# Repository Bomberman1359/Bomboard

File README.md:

# Bomboard
This is my cost efficient, custom keyboard made by me. As my first project, I named it Bomboard.

I made this project not only for the Highway programs, but also to gain experience in creating my own electronics.
I wanted to learn more about schematics, wiring, PCB, and 3D modeling. As someone that does not spend money on buying keyboards I figured it would be cool to create my own!

## Schematic

## PCB

## Case

## Case and PCB combined 

## BOM
|    Item    | Quantity | Vendor | Total Price |
| :-------- | :-------: | :----- | ----------: |
| PCB | 1 | JLCPB | $74.23 |
| Raspberry Pi Pico | 1 | [Seeed Studio](https://www.seeedstudio.com/Raspberry-Pi-Pico-2-p-5940.html?srsltid=AfmBOopNDN0RoseM_BDfpGL9q782IZnb89sHLu-LgA_pmGtyh8bIAI12ZJQ&gQT=2) | $5.00 |
| Key switches |  64  |  [Mechanical](https://mechanicalkeyboards.com/products/cherry-mx2a-blue-60g-clicky?_pos=1&_fid=016d7ed23&_ss=c)| $25.60 |
| Rotary Encoder | 1    | [SynthCube](https://synthcube.com/rotary-encoder/?gQT=1) | $2.95 | 
| Stabilizer set | 1 | [Divinikey](https://jlcpcb.com/) | $11.00 |
| Keycaps Set| 1 | [Amazon](https://www.amazon.com/Womier-Pudding-Keycaps-100-Percent/dp/B0DB4Z6DMS/ref=sr_1_4?crid=3KDSGFET7R3PW&dib=eyJ2IjoiMSJ9.JXTwjGdToK3WZEH4x7wFjjcMgp3TTPoNjdzpdxdQVgSHMkKCM3K1UQXigcpua9MdYIqJtKjmeekwVAu9vGDxT6nALVuQltDVwMgUqYsUHxBDTm3vLYU9XO3WX6_CRoCUf1UHvEwgMiXLOVtKKSAhyrsmoaTP-IWt4scI0ptknhSZiXKoMoXzRBTZNzhqpnvYZ7vWStdUbOes3QbC9iO88euB4x_6QWYsmUlvxiN9ol6HuYmnZpW-kDZQ4B3cP-TrFnPHNfEt-rMB7Xzw2pRuJncPvS_wAUjKVpEICK8Bqcc.ESKlCixw82J9ZDOgV03xSDnqUloHnb8AKA523uXzZJI&dib_tag=se&keywords=normal%2Bkey%2Bcaps&qid=1751660071&s=electronics&sprefix=normal%2Bkey%2Bcaps%2Celectronics%2C144&sr=1-4&th=1) | $14.99 |

Net Total Cost: $133.77

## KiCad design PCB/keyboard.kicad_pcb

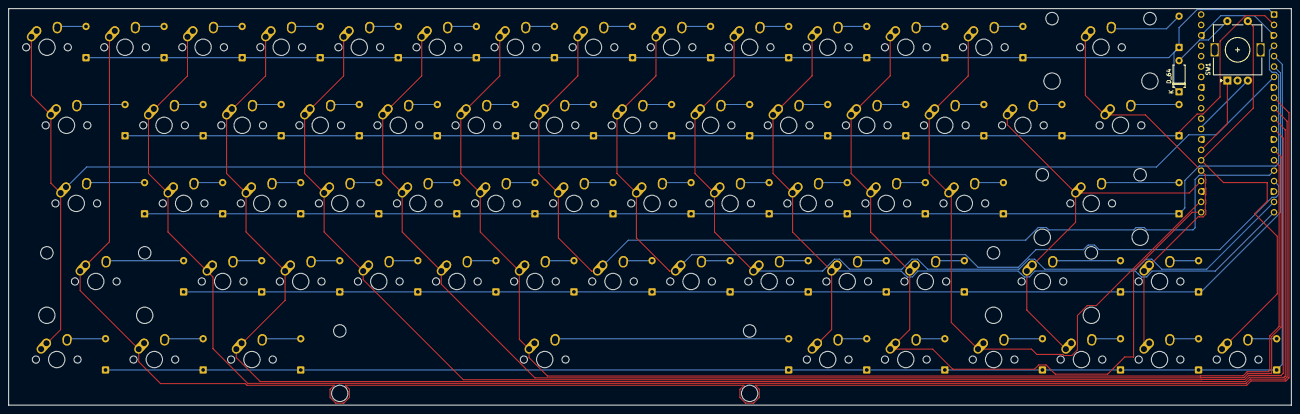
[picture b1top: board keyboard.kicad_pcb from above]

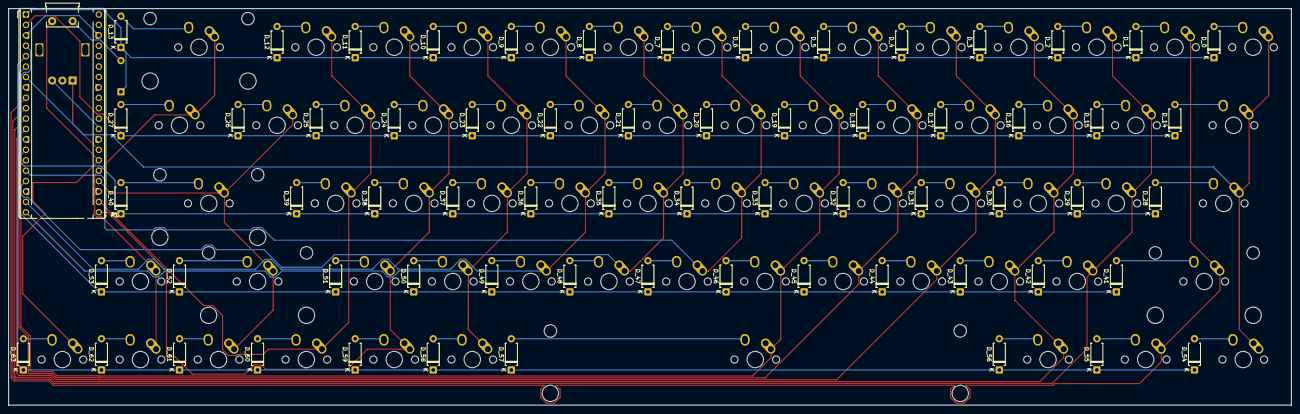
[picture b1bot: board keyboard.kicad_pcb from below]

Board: 2 copper layers, 313.0 x 96.8 mm, 131 parts (65 on the bottom side), 89 nets.

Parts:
A1: RaspberryPi_Pico; RaspberryPi_Pico_Common_THT
D_0, D_1, D_2, D_3, D_4, D_5, D_6, D_7, D_8, D_9, D_10, D_11, D_12, D_13, D_14, D_15, D_16, D_17, D_18, D_19, D_20, D_21, D_22, D_23, D_24, D_25, D_26, D_27, D_28, D_29, D_30, D_31, D_32, D_33, D_34, D_35, D_36, D_37, D_38, D_39, D_40, D_41, D_42, D_43, D_44, D_45, D_46, D_47, D_48, D_49, D_50, D_51, D_52, D_53, D_54, D_55, D_56, D_57, D_58, D_59, D_60, D_61, D_62, D_63, D_64: D; D_A-405_P7.62mm_Horizontal
K_0, K_1, K_2, K_3, K_4, K_5, K_6, K_7, K_8, K_9, K_10, K_11, K_12, K_15, K_16, K_17, K_18, K_19, K_20, K_21, K_22, K_23, K_24, K_25, K_26, K_29, K_30, K_31, K_32, K_33, K_34, K_35, K_36, K_37, K_38, K_39, K_42, K_43, K_44, K_45, K_46, K_47, K_48, K_49, K_50, K_51, K_53, K_58, K_59, K_61, K_62, K_63: KEYSW; MX-1U-NoLED
K_13, K_52: KEYSW; MX-2U-NoLED
K_14, K_27: KEYSW; MX-1.5U-NoLED
K_28: KEYSW; MX-1.75U-NoLED
K_40, K_41: KEYSW; MX-2.25U-NoLED
K_54, K_55, K_56, K_60: KEYSW; MX-1.25U-NoLED
K_57: KEYSW; MX-6.25U-NoLED
SW1: RotaryEncoder_Switch; RotaryEncoder_Alps_EC11E-Switch_Vertical_H20mm

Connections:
1A: A1.27 (GPIO21), SW1.A
1B: A1.29 (GPIO22), SW1.B
unnamed: A1.3 (GND), A1.8 (GND), A1.13 (GND), A1.18 (GND), A1.23 (GND), A1.28 (GND), A1.38 (GND)
unnamed: D_0.2 (A), K_0.2 (ROW)
unnamed: D_1.2 (A), K_1.2 (ROW)
unnamed: D_2.2 (A), K_2.2 (ROW)
unnamed: D_3.2 (A), K_3.2 (ROW)
unnamed: D_4.2 (A), K_4.2 (ROW)
unnamed: D_5.2 (A), K_5.2 (ROW)
unnamed: D_6.2 (A), K_6.2 (ROW)
unnamed: D_7.2 (A), K_7.2 (ROW)
unnamed: D_8.2 (A), K_8.2 (ROW)
unnamed: D_9.2 (A), K_9.2 (ROW)
unnamed: D_10.2 (A), K_10.2 (ROW)
unnamed: D_11.2 (A), K_11.2 (ROW)
unnamed: D_12.2 (A), K_12.2 (ROW)
unnamed: D_13.2 (A), K_13.2 (ROW)
unnamed: D_14.2 (A), K_14.2 (ROW)
unnamed: D_15.2 (A), K_15.2 (ROW)
unnamed: D_16.2 (A), K_16.2 (ROW)
unnamed: D_17.2 (A), K_17.2 (ROW)
unnamed: D_18.2 (A), K_18.2 (ROW)
unnamed: D_19.2 (A), K_19.2 (ROW)
unnamed: D_20.2 (A), K_20.2 (ROW)
unnamed: D_21.2 (A), K_21.2 (ROW)
unnamed: D_22.2 (A), K_22.2 (ROW)
unnamed: D_23.2 (A), K_23.2 (ROW)
unnamed: D_24.2 (A), K_24.2 (ROW)
unnamed: D_25.2 (A), K_25.2 (ROW)
unnamed: D_26.2 (A), K_26.2 (ROW)
unnamed: D_27.2 (A), K_27.2 (ROW)
unnamed: D_28.2 (A), K_28.2 (ROW)
unnamed: D_29.2 (A), K_29.2 (ROW)
unnamed: D_30.2 (A), K_30.2 (ROW)
unnamed: D_31.2 (A), K_31.2 (ROW)
unnamed: D_32.2 (A), K_32.2 (ROW)
unnamed: D_33.2 (A), K_33.2 (ROW)
unnamed: D_34.2 (A), K_34.2 (ROW)
unnamed: D_35.2 (A), K_35.2 (ROW)
unnamed: D_36.2 (A), K_36.2 (ROW)
unnamed: D_37.2 (A), K_37.2 (ROW)
unnamed: D_38.2 (A), K_38.2 (ROW)
unnamed: D_39.2 (A), K_39.2 (ROW)
unnamed: D_40.2 (A), K_40.2 (ROW)
unnamed: D_41.2 (A), K_41.2 (ROW)
unnamed: D_42.2 (A), K_42.2 (ROW)
unnamed: D_43.2 (A), K_43.2 (ROW)
unnamed: D_44.2 (A), K_44.2 (ROW)
unnamed: D_45.2 (A), K_45.2 (ROW)
unnamed: D_46.2 (A), K_46.2 (ROW)
unnamed: D_47.2 (A), K_47.2 (ROW)
unnamed: D_48.2 (A), K_48.2 (ROW)
unnamed: D_49.2 (A), K_49.2 (ROW)
unnamed: D_50.2 (A), K_50.2 (ROW)
unnamed: D_51.2 (A), K_51.2 (ROW)
unnamed: D_52.2 (A), K_52.2 (ROW)
unnamed: D_53.2 (A), K_53.2 (ROW)
unnamed: D_54.2 (A), K_54.2 (ROW)
unnamed: D_55.2 (A), K_55.2 (ROW)
unnamed: D_56.2 (A), K_56.2 (ROW)
unnamed: D_57.2 (A), K_57.2 (ROW)
unnamed: D_58.2 (A), K_58.2 (ROW)
unnamed: D_59.2 (A), K_59.2 (ROW)
unnamed: D_60.2 (A), K_60.2 (ROW)
unnamed: D_61.2 (A), K_61.2 (ROW)
unnamed: D_62.2 (A), K_62.2 (ROW)
unnamed: D_63.2 (A), K_63.2 (ROW)
unnamed: D_64.2 (A), SW1.S2
col0: A1.7 (GPIO5), K_0.1 (COL), K_14.1 (COL), K_28.1 (COL), K_54.1 (COL)
col1: A1.9 (GPIO6), K_1.1 (COL), K_41.1 (COL), K_55.1 (COL)
col2: A1.10 (GPIO7), K_2.1 (COL), K_15.1 (COL), K_29.1 (COL), K_42.1 (COL)
col3: A1.11 (GPIO8), K_3.1 (COL), K_16.1 (COL), K_30.1 (COL), K_43.1 (COL), K_56.1 (COL)
col4: A1.12 (GPIO9), K_4.1 (COL), K_17.1 (COL), K_31.1 (COL), K_44.1 (COL)
col5: A1.14 (GPIO10), K_5.1 (COL), K_18.1 (COL), K_32.1 (COL), K_45.1 (COL)
col6: A1.15 (GPIO11), K_6.1 (COL), K_19.1 (COL), K_33.1 (COL), K_46.1 (COL), K_57.1 (COL)
col7: A1.16 (GPIO12), K_7.1 (COL), K_20.1 (COL), K_34.1 (COL), K_47.1 (COL)
col8: A1.17 (GPIO13), K_8.1 (COL), K_21.1 (COL), K_35.1 (COL), K_48.1 (COL)
col9: A1.19 (GPIO14), K_9.1 (COL), K_22.1 (COL), K_36.1 (COL), K_49.1 (COL)
col10: A1.20 (GPIO15), K_10.1 (COL), K_23.1 (COL), K_37.1 (COL), K_50.1 (COL), K_58.1 (COL)
col11: A1.21 (GPIO16), K_11.1 (COL), K_24.1 (COL), K_38.1 (COL), K_51.1 (COL), K_59.1 (COL)
col12: A1.22 (GPIO17), K_12.1 (COL), K_25.1 (COL), K_39.1 (COL), K_60.1 (COL)
col13: A1.24 (GPIO18), K_26.1 (COL), K_40.1 (COL), K_52.1 (COL), K_61.1 (COL)
col14: A1.25 (GPIO19), K_13.1 (COL), K_27.1 (COL), K_53.1 (COL), K_62.1 (COL)
col15: A1.26 (GPIO20), K_63.1 (COL), SW1.S1
row0: A1.1 (GPIO0), D_0.1 (K), D_1.1 (K), D_2.1 (K), D_3.1 (K), D_4.1 (K), D_5.1 (K), D_6.1 (K), D_7.1 (K), D_8.1 (K), D_9.1 (K), D_10.1 (K), D_11.1 (K), D_12.1 (K), D_13.1 (K), D_64.1 (K)
row1: A1.2 (GPIO1), D_14.1 (K), D_15.1 (K), D_16.1 (K), D_17.1 (K), D_18.1 (K), D_19.1 (K), D_20.1 (K), D_21.1 (K), D_22.1 (K), D_23.1 (K), D_24.1 (K), D_25.1 (K), D_26.1 (K), D_27.1 (K)
row2: A1.4 (GPIO2), D_28.1 (K), D_29.1 (K), D_30.1 (K), D_31.1 (K), D_32.1 (K), D_33.1 (K), D_34.1 (K), D_35.1 (K), D_36.1 (K), D_37.1 (K), D_38.1 (K), D_39.1 (K), D_40.1 (K)
row3: A1.6 (GPIO4), D_41.1 (K), D_42.1 (K), D_43.1 (K), D_44.1 (K), D_45.1 (K), D_46.1 (K), D_47.1 (K), D_48.1 (K), D_49.1 (K), D_50.1 (K), D_51.1 (K), D_52.1 (K), D_53.1 (K)
row4: A1.5 (GPIO3), D_54.1 (K), D_55.1 (K), D_56.1 (K), D_57.1 (K), D_58.1 (K), D_59.1 (K), D_60.1 (K), D_61.1 (K), D_62.1 (K), D_63.1 (K)

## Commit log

2025-07-04 Add files via upload
    Actual CAD information
2025-07-06 Create stuff
2025-07-06 Update stuff
2025-07-07 Adding the PCB file with all of the PCB information
2025-07-07 Organizing everything into the firmware and case files
2025-07-08 Final organization
2025-07-08 Adding step files of the different parts of the case
